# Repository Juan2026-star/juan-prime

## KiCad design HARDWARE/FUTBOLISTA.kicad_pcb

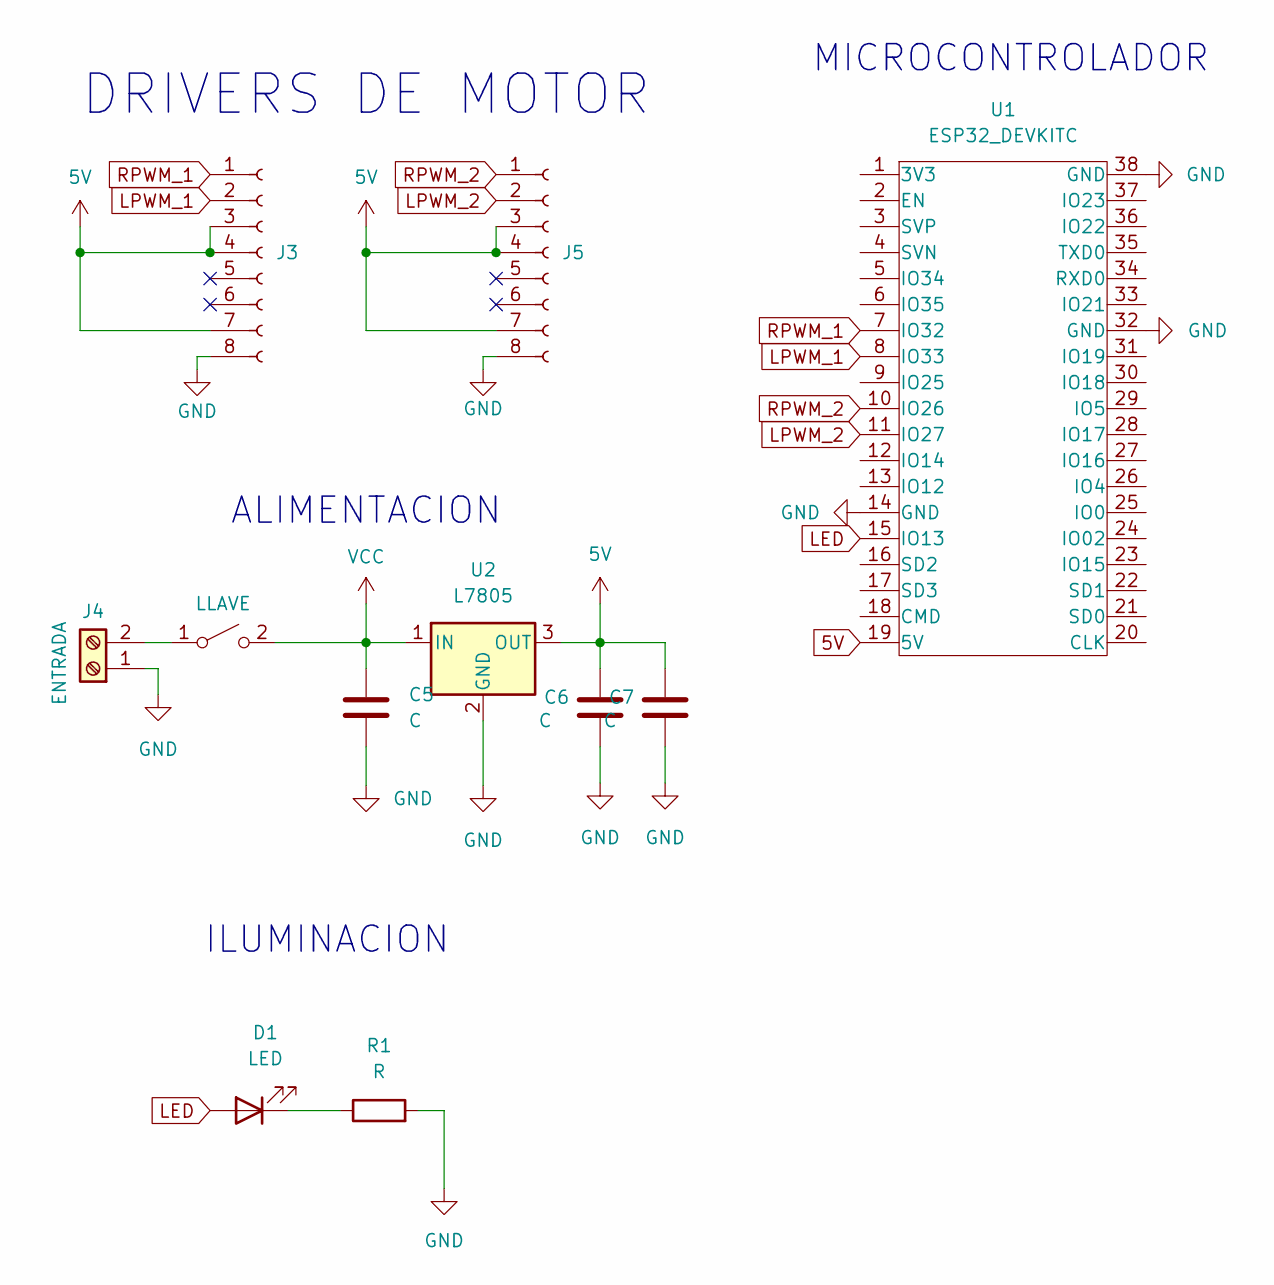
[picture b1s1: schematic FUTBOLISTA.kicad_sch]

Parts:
C5, C6: C; C_0805_2012Metric_Pad1.18x1.45mm_HandSolder
C7: C; CAP_ELEC_5x11mm
D1: LED; led_5mm_clear
J3, J5: Conn_01x08_Socket; IDC-Header_2x04_P2.54mm_Vertical
J4: ENTRADA; AMASS_XT30U-F_1x02_P5.0mm_Vertical
LLAVE1: LLAVE; SW_PUSH_1P1T_6x3.5mm_H5.0_APEM_MJTP1250
R1: R; R_0805_2012Metric_Pad1.20x1.40mm_HandSolder
U1: ESP32_DEVKITC; esp32 38 pin usb-c
U2: L7805; TO-263-3_TabPin2

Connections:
5V: C6.1, C7.1, J3.3, J3.4, J3.7, J5.3, J5.4, J5.7, U1.19 (5V), U2.3 (OUT)
GND: C5.2, C6.2, C7.2, J3.8, J4.1, J5.8, R1.2, U1.14 (GND), U1.32 (GND), U1.38 (GND), U2.2 (GND)
LED: D1.2 (A), U1.15 (IO13)
LPWM_1: J3.2, U1.8 (IO33)
LPWM_2: J5.2, U1.11 (IO27)
unnamed: D1.1 (K), R1.1
unnamed: J4.2, LLAVE1.1 (A)
RPWM_1: J3.1, U1.7 (IO32)
RPWM_2: J5.1, U1.10 (IO26)
VCC: C5.1, LLAVE1.2 (B), U2.1 (IN)

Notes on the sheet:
MICROCONTROLADOR
ALIMENTACION
DRIVERS DE MOTOR
ILUMINACION

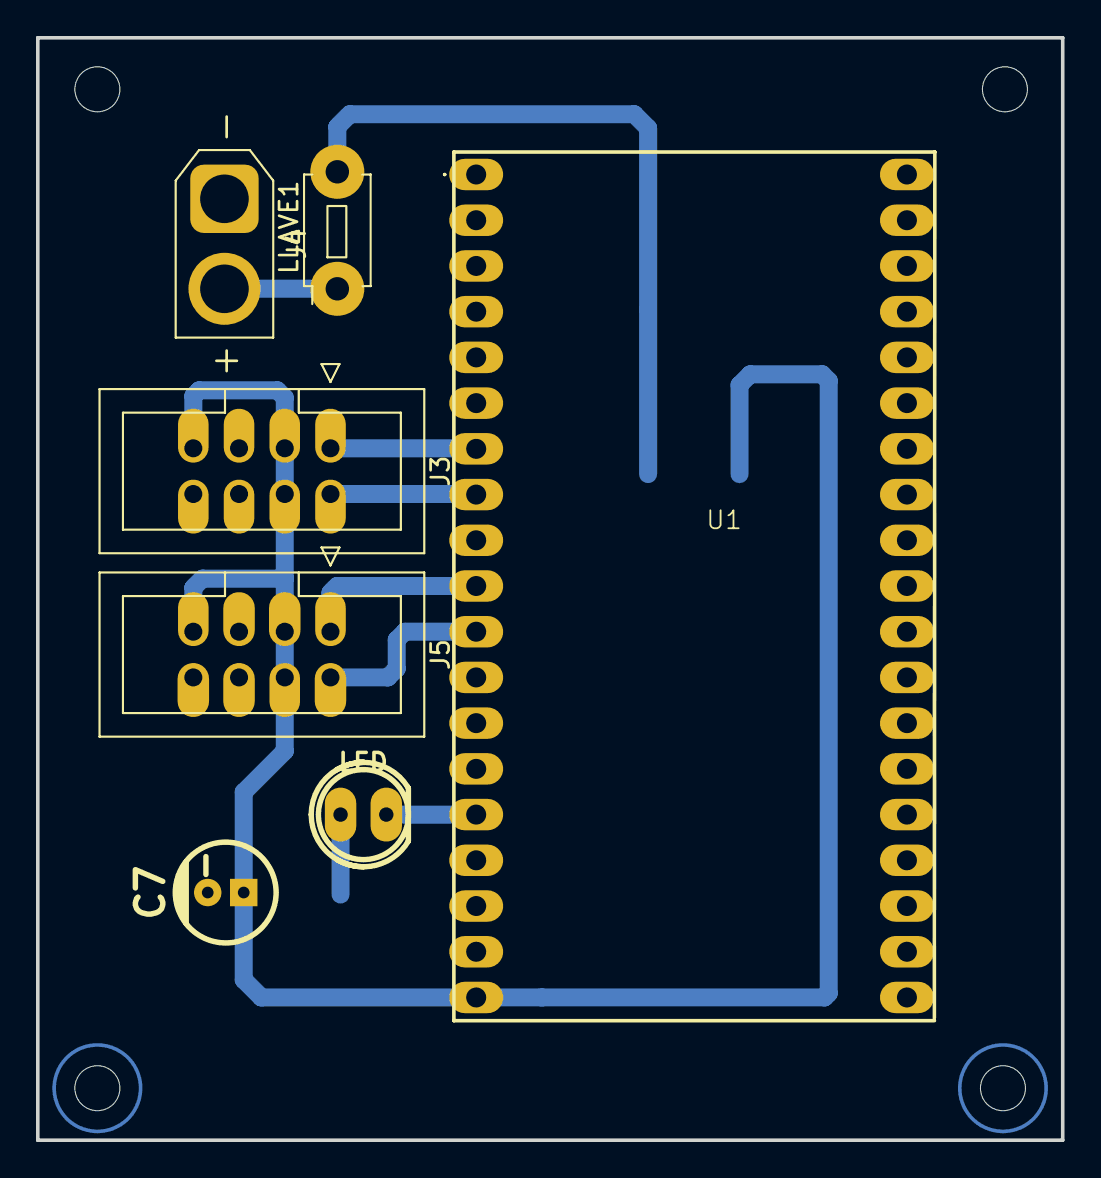
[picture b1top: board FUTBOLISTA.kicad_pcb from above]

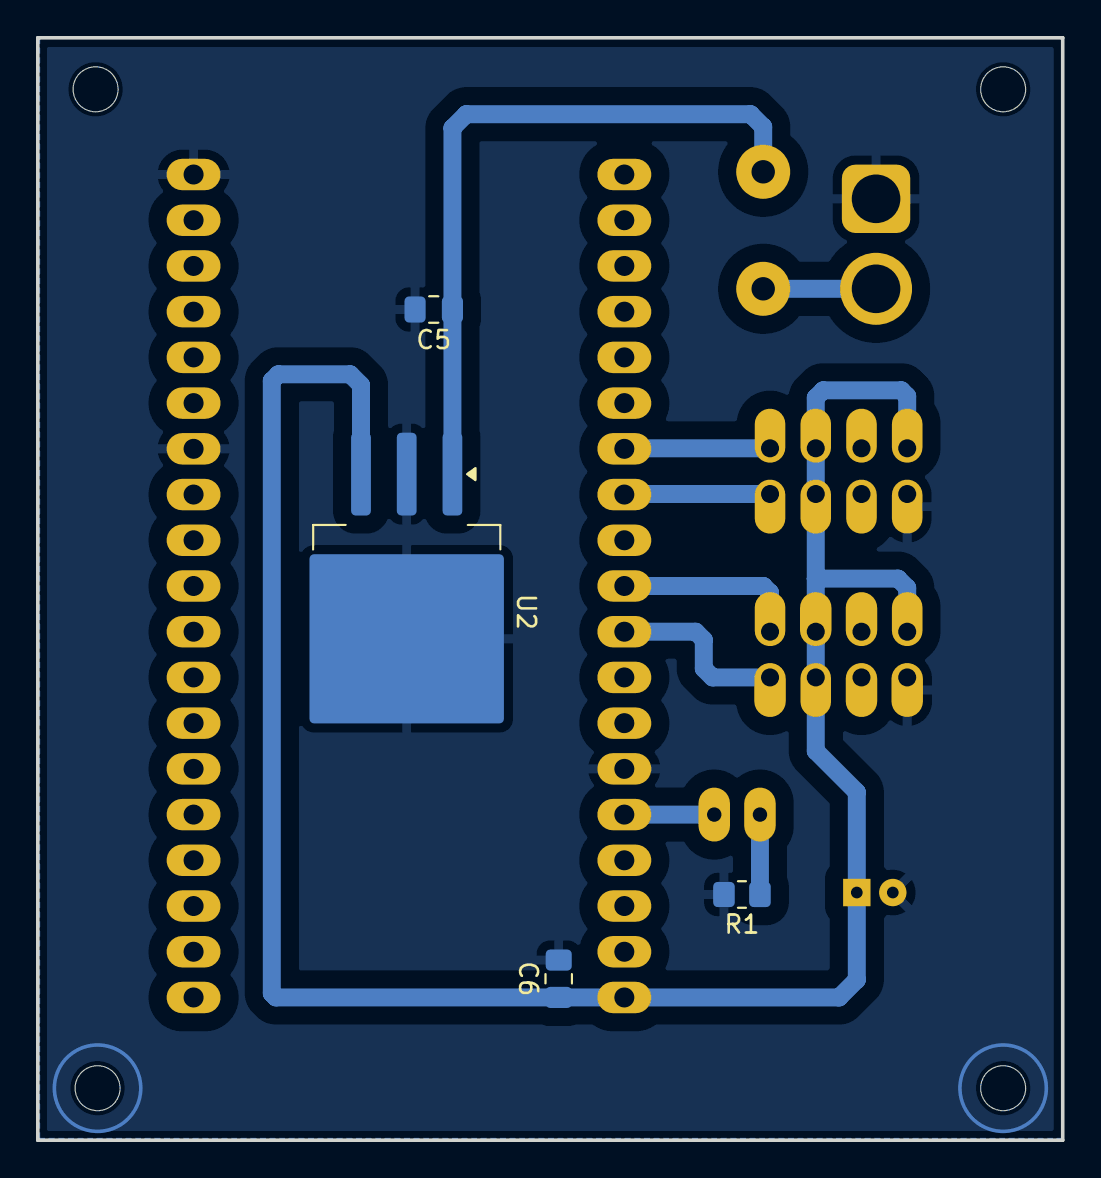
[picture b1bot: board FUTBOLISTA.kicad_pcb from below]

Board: 2 copper layers, 56.9 x 61.2 mm, 11 parts (4 on the bottom side), 10 nets.

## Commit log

2026-03-17 mi primer commit
2026-03-17 Modificamos titulo en index.html
